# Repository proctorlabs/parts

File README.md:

# SCAD Library

Just some of my SCAD objects

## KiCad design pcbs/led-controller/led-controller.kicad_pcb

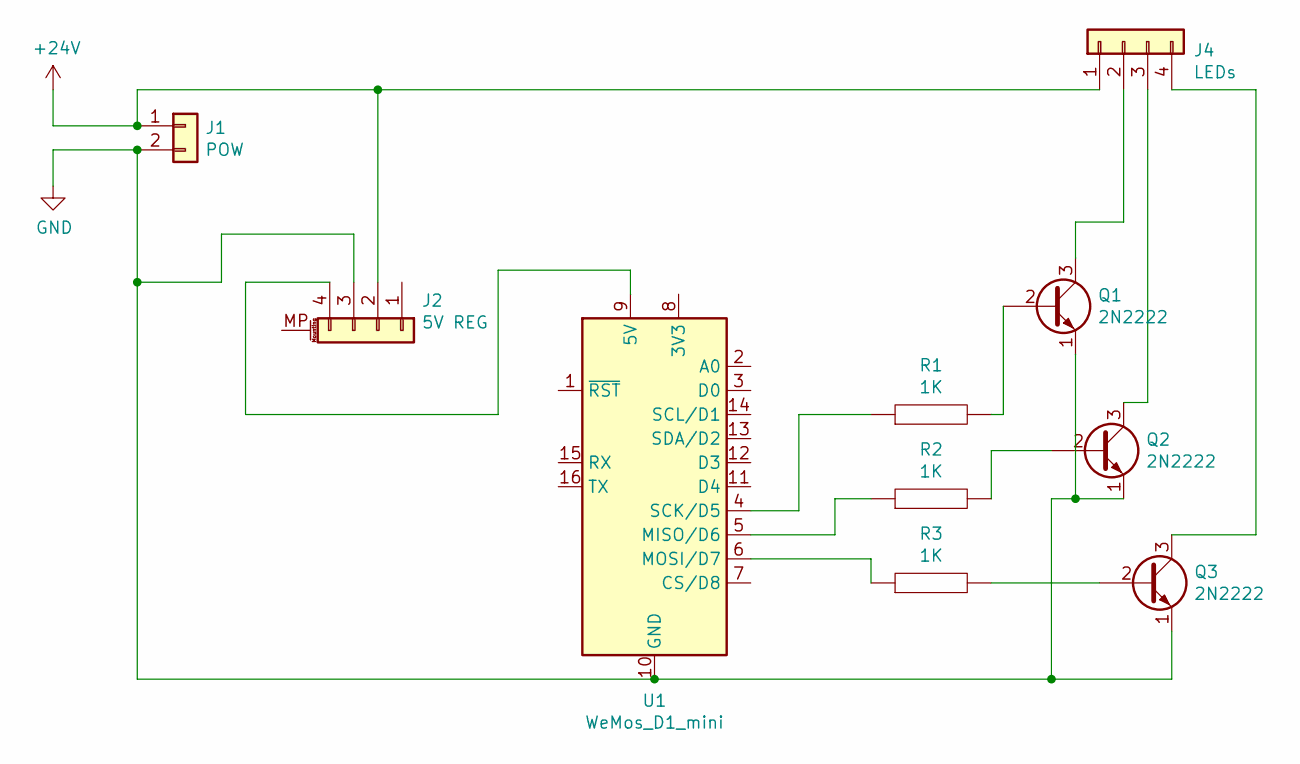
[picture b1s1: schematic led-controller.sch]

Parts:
J1: POW; PinHeader_1x02_P2.54mm_Vertical
J2: 5V REG; PinHeader_1x04_P2.54mm_Vertical
J4: LEDs; PinHeader_1x04_P2.54mm_Vertical
Q1, Q2, Q3: 2N2222; TO-39-3
R1, R2, R3: 1K; R_Box_L8.4mm_W2.5mm_P5.08mm
U1: WeMos_D1_mini; WEMOS_D1_mini_light

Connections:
+24V: J1.1, J2.2, J4.1
GND: J1.2, J2.3, Q1.1 (E), Q2.1 (E), Q3.1 (E), U1.10 (GND)
unnamed: J2.4, U1.9 (5V)
unnamed: J4.2, Q1.3 (C)
unnamed: J4.3, Q2.3 (C)
unnamed: J4.4, Q3.3 (C)
unnamed: Q1.2 (B), R1.2
unnamed: Q2.2 (B), R2.2
unnamed: Q3.2 (B), R3.2
unnamed: R1.1, U1.4 (SCK/D5)
unnamed: R2.1, U1.5 (MISO/D6)
unnamed: R3.1, U1.6 (MOSI/D7)

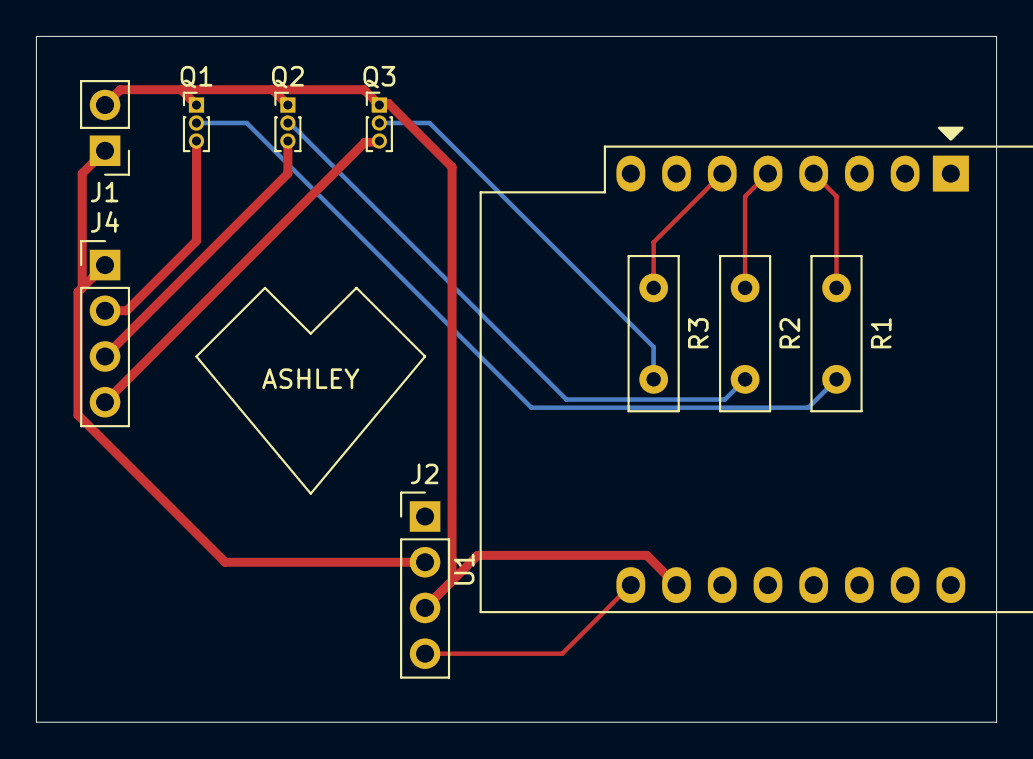
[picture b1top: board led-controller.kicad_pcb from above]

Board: 2 copper layers, 53.3 x 38.1 mm, 10 parts (0 on the bottom side), 12 nets.

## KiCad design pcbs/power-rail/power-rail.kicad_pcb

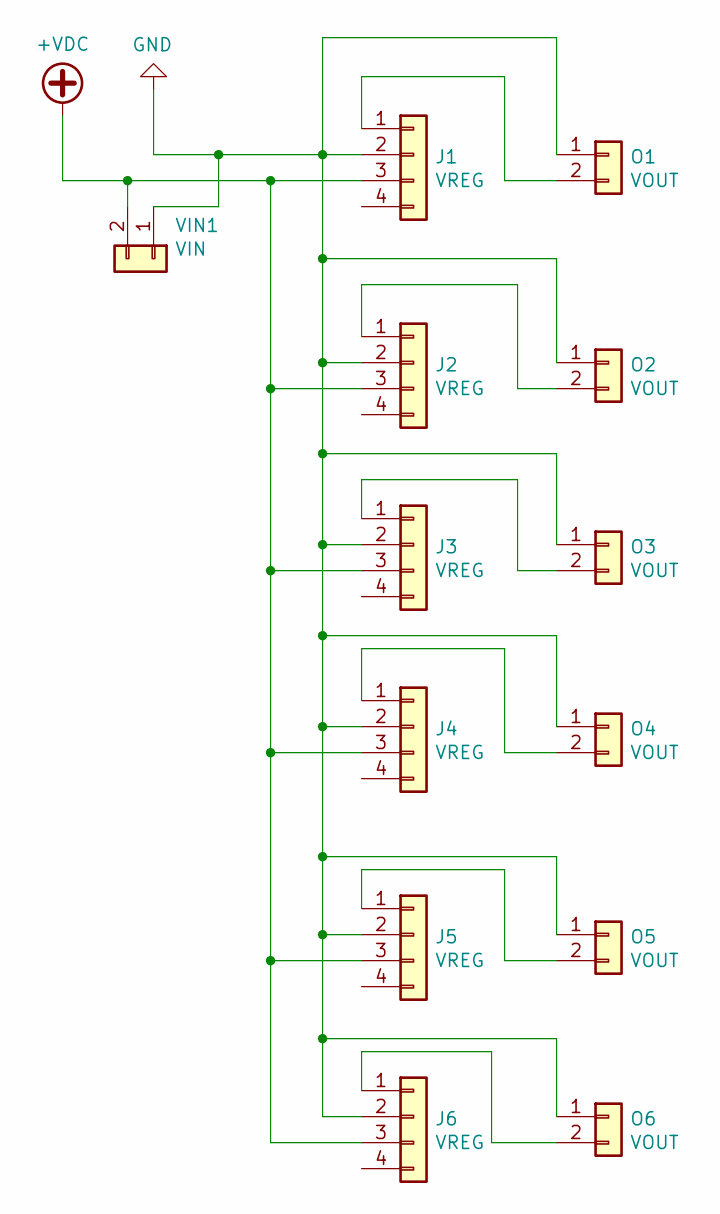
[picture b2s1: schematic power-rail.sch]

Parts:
J1, J2, J3, J4, J5, J6: VREG; PinHeader_1x04_P2.54mm_Vertical
O1, O2, O3, O4, O5, O6: VOUT; PinHeader_1x02_P2.54mm_Vertical
VIN1: VIN; PinSocket_2x06_P2.54mm_Vertical

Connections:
+VDC: J1.3, J2.3, J3.3, J4.3, J5.3, J6.3, VIN1.2
GND: J1.2, J2.2, J3.2, J4.2, J5.2, J6.2, O1.1, O2.1, O3.1, O4.1, O5.1, O6.1, VIN1.1
unnamed: J1.1, O1.2
unnamed: J2.1, O2.2
unnamed: J3.1, O3.2
unnamed: J4.1, O4.2
unnamed: J5.1, O5.2
unnamed: J6.1, O6.2

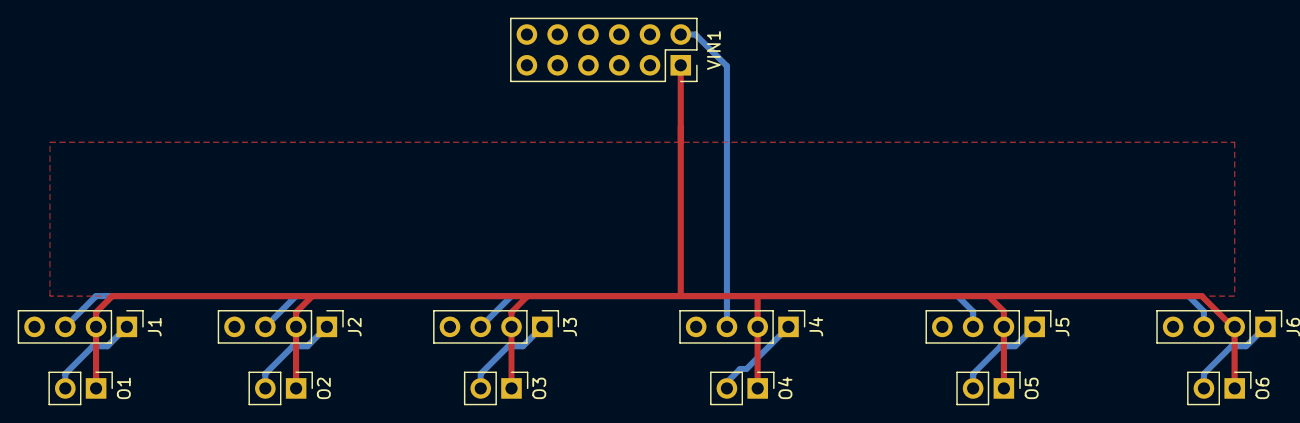
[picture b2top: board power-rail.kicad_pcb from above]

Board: 2 copper layers, 13 parts (0 on the bottom side), 8 nets.

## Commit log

2020-01-14 WIP relay box
2020-01-14 Converted to SolidPython
2020-01-14 README.md
2020-01-15 Compartmentalized the components and added most of the parts to the ESP relay prototype
2020-01-17 MCAD template added
2020-01-17 Comment adding dimensions for AC/DC converter
2020-01-20 Added wire guides, mounting screws
2020-10-09 Added a few new parts and customizable scad models
2020-10-26 Added project case model, in progress 3d printer build
2020-12-17 Checkin previous models
2021-01-31 Updated models, PCB Holder added, Rack Rail
2021-04-24 Checkin for old changes
2021-06-24 Checkin for room sensor
2021-06-25 Added DIN clip and tray
2021-06-28 Battery pack, glass joints added
